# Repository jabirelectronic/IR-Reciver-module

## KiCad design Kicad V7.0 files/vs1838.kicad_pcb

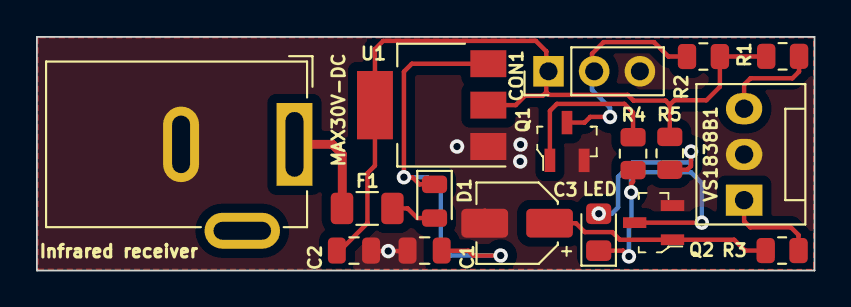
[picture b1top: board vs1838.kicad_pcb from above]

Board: 2 copper layers, 43.2 x 13.0 mm, 17 parts (0 on the bottom side), 12 nets.

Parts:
C1, C2: 100nF_0603_16V; C_0805_2012Metric
C3: 47uF_5x5.3_16V; CP_Elec_4x3
CON1: Conn_01x03; PinHeader_1x03_P2.54mm_Vertical
D1: M7; D_0805_2012Metric
F1: Fuse; Fuse_1206_3216Metric
LED: L; LED_0805_2012Metric_Pad1.15x1.40mm_HandSolder
MAX30V-DC: Barrel_Jack_MountingPin; BarrelJack_GCT_DCJ200-10-A_Horizontal
Q1, Q2: BC817; SOT-23-3
R1, R2, R3, R4, R5: 68R_0805_350mW; R_0805_2012Metric
U1: AMS1117-5.0; SOT-223-3_TabPin2
VS1838B1: Conn_01x03; FanPinHeader_1x03_P2.54mm_Vertical

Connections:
Earth: C1.2, C2.2, C3.2, CON1.3, MAX30V-DC.2, Q1.2 (E), Q2.2 (E), U1.1 (GND), VS1838B1.2
unnamed: C2.1, CON1.1, R1.2, R2.2, R5.1, U1.2 (VO)
unnamed: CON1.2, Q1.3 (C), R2.1
unnamed: D1.2 (A), F1.2
unnamed: C1.1, D1.1 (K), U1.3 (VI)
unnamed: F1.1, MAX30V-DC.1
unnamed: LED.2 (A), R5.2
unnamed: LED.1 (K), Q2.3 (C), R4.1
unnamed: Q1.1 (B), R4.2
unnamed: C3.1, Q2.1 (B), R3.2
unnamed: R3.1, VS1838B1.1
unnamed: R1.1, VS1838B1.3

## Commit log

2023-02-20 add project
2023-02-25 Rename Project details.txt to README.md
